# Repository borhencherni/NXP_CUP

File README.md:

**NXP Cup Robot**  
This repository contains the software, electronics, mechanical references, and documentation for the NXP Cup lane-following competition robot.  
   
 The current implementation is centered on two main embedded targets:  
- a Teensy 4.0 control unit that handles line tracking, steering, motor control, and telemetry generation  
- an ESP32 interface board that provides a web dashboard, manual drive controls, and live trajectory visualization  
**Project Overview 🤖**  
The robot is designed to follow a track as consistently and efficiently as possible while remaining debuggable during development.  
   
 The software is organized so that the core logic is separated into small header/source modules, making the control flow easier to maintain and inspect.  
   
 The goal of this document is to describe the robot, the role of each code part, and the current development phases in a way that matches the actual project structure.  
**System Architecture ⚙️**  
**Teensy 4.0 🧠**  
The Teensy is the main real-time controller. It is responsible for:  
- reading the Pixy2 line camera data  
- normalizing and fusing detected line vectors  
- computing a lookahead point for steering  
- applying PID-style steering correction  
- detecting lane sides and special line patterns  
- driving the motors and steering servo  
- reading the ultrasonic distance sensor  
- sending telemetry packets to the ESP32 over UART  
The Teensy code is organized into focused modules under NXPcup/include and NXPcup/src/teensy:  
- teensy_config.h for constants, pins, and tuning values  
- teensy_state.h and teensy_state.cpp for shared robot state  
- teensy_motors.h and teensy_motors.cpp for motor and servo output  
- teensy_sensors.h and teensy_sensors.cpp for ultrasonic sensing  
- teensy_vision.h and teensy_vision.cpp for Pixy2 processing and steering logic  
- main_teensy.cpp as the control entrypoint  
**ESP32 Interface 🌐**  
The ESP32 acts as the operator interface and telemetry gateway. It is responsible for:  
- receiving telemetry packets from the Teensy through UART  
- exposing a Wi-Fi access point  
- serving a browser-based control dashboard  
- sending manual drive commands back to the Teensy  
- drawing the robot trajectory in real time from received points  
The ESP32 code is organized into:  
- esp_config.h for UART and access point settings  
- esp_telemetry.h and esp_telemetry.cpp for packet parsing, point history, and command forwarding  
- esp_web.h and esp_web.cpp for the HTML interface and HTTP routes  
- main_esp.cpp as the entrypoint  
**Control Logic 🧭**  
The Teensy control loop follows a clear sequence:  
1. Read all Pixy2 line features  
2. Normalize line vector direction  
3. Fuse valid vectors into a single motion estimate  
4. Normalize the fused vector  
5. Compute an adaptive lookahead point  
6. Convert the lookahead error into steering correction  
7. Apply lane-side correction when only one side of the track is visible  
8. Clamp and smooth the servo command  
9. Drive the motors  
10. Send telemetry to the ESP32  
The telemetry packet format is:  
D,vx,vy,steeringangle,servoangle  
The ESP32 manual command format is:  
C,<command>  
Where the current commands are:  
- F for forward  
- B for backward  
- L for left  
- R for right  
- S for stop  
The current control strategy focuses on lane following and smooth steering.  
   
 The robot can be further developed by adding velocity regulation and speed profiling, in the style of the code asservissement vitesse approach, to keep the speed more stable across straights, curves, and transitions.  
**Phases Of Working 🔄**  
**1. Perception**  
The Pixy2 camera runs in line-tracking mode and the Teensy extracts track geometry from the visible vectors.  
   
 This phase focuses on identifying the path, rejecting noise, and understanding sharp turns, lane boundaries, and horizontal markers.  
**2. Motion Estimation**  
The detected vectors are filtered and fused into a single direction estimate.  
   
 A lookahead point is then computed so the robot can react smoothly on straights and more aggressively in curves.  
**3. Steering And Drive Control**  
The steering output is computed from the lookahead error and adjusted with PID-style terms.  
   
 The motor speed and servo angle are then constrained to keep motion stable.  
**4. Telemetry And Debugging**  
The Teensy sends live telemetry to the ESP32 so the robot can be observed while running.  
   
 This data includes vector direction, steering output, and servo angle.  
**5. Operator Interface**  
The ESP32 hosts a browser dashboard with manual drive buttons and a live trace of the robot path.  
   
 The LED status indicator changes color based on whether telemetry is being received.  
**6. Mechanical And Electrical Integration**  
The CAD, PCB, and wiring notes are used to assemble the chassis, sensors, drivetrain, and electronics reliably.  
   
 This phase ties the software to the physical robot.  
**Mechanical Part 🛠️**  
The mechanical part covers the chassis, steering, drivetrain, and mounting system.  
   
 These references are useful for assembly, servicing, and mechanical debugging.  
**Robot Assembly**  
**Mechanical Design**  
**Electrical Part ⚡**  
The electrical part covers the wiring, PCB layout, power distribution, and interface hardware.  
   
 These elements support the sensors, controller, motor driver, and communication links.  
**System Schematic**  
**PCB Routing**  
**PCB Overview**  
**Validation Videos 🎥**  
The following videos are used to validate different layers of the system during development:  
- video for the robot completing one lap.mp4 for the robot completing one lap  
- video for the robot stopping when detecting the box.mp4 for the robot stopping test  
**Pins And Hardware Notes 📌**  
Current Teensy pin usage:  
- motor inputs: 22, 23, 6, 7  
- servo output: 8  
- ultrasonic trigger: 18  
- ultrasonic echo: 19  
The project uses:  
- Teensy 4.0 as the controller  
- Pixy2 in line mode  
- steering servo  
- H-bridge motor driver  
- ultrasonic distance sensor  
- ESP32 for telemetry and control UI  
**Web Interface 🖥️**  
The ESP32 dashboard uses a dark industrial theme based on black, white, and #AA0000 red accents.  
   
 It includes:  
- forward, backward, left, right, and stop buttons  
- a circular ESP badge with a connection LED  
- live telemetry readouts  
- a black canvas with a white trail showing the robot path in real time  
**Web Interface Preview**  
**Software Layout 💻**  
The main source folders are:  
- NXPcup/src/teensy for the Teensy 4.0 control code  
- NXPcup/src/esp for the ESP32 dashboard and UART bridge  
- NXPcup/include for shared headers and configuration  
- NXPcup/lib for legacy or reusable helper sources  
- notes for pinout and power notes  
- Mécanique for CAD and mechanical references  
**Code Roles 🧩**  
The code is split so each module has a clear role in the robot:  
- main_teensy.cpp runs the full real-time control loop and coordinates perception, steering, drive output, and telemetry  
- teensy_vision.cpp handles Pixy2 processing, vector fusion, lane detection, and steering computation  
- teensy_motors.cpp converts high-level speed commands into motor outputs and servo control  
- teensy_sensors.cpp reads the ultrasonic sensor used for distance checking  
- teensy_state.cpp stores the shared robot state used by the other Teensy modules  
- main_esp.cpp initializes the ESP32 system and connects the web dashboard to UART telemetry  
- esp_telemetry.cpp parses telemetry packets, stores path points, and forwards manual commands  
- esp_web.cpp serves the browser interface, controls the buttons, and draws the live ride trace  
**Development Note 🚀**  
The robot can also be extended with velocity regulation and speed profiling in the style of code asservissement vitesse to stabilize motion across straights, curves, and transitions.  
**Power And Wiring Notes 🔌**  
The project notes indicate the following supply plan:  
- Teensy: 5V  
- camera: external 5V  
- servo: external 5V  
- motors: 12V  
- ultrasonic sensor: 3.3V  
- logic and power grounds must be shared where required  
**Build And Run 🏗️**  
The PlatformIO project is configured for the Teensy environment in NXPcup/platformio.ini.  
   
 Typical workflow:  
1. open the NXPcup folder in PlatformIO or VS Code  
2. build the Teensy environment  
3. upload to the Teensy board  
4. power the ESP32 and open the Wi-Fi dashboard  
5. watch the telemetry stream and path trace in the browser  
Example build command:  
cd NXPcup  
 platformio run -e teensy40  
   
**Resources 📚**  
- [Enseirb NXP Cup 2019 ](https://github.com/Enseirb-NXP-Cup-2019/cars/blob/master/src/Arduino/suivi_piste.ino "https://github.com/Enseirb-NXP-Cup-2019/cars/blob/master/src/Arduino/suivi_piste.ino")  
- [Enseirb NXP Cup 2019 website](https://github.com/Enseirb-NXP-Cup-2019/nxpcup.enseirb.github.io?tab=readme-ov-file "https://github.com/Enseirb-NXP-Cup-2019/nxpcup.enseirb.github.io?tab=readme-ov-file")  
- [Electromaker NXP Cup project](https://www.electromaker.io/project/view/nxp-cup-project "https://www.electromaker.io/project/view/nxp-cup-project")  
- [NXP-CUP-FINALS](https://github.com/aminebensaid66/NXP-CUP-FINALS "https://github.com/aminebensaid66/NXP-CUP-FINALS")  
**Notes 📝**  
This documentation reflects the current modularized Teensy and ESP32 codebase.  
   
 It is intended to help with debugging, maintenance, and competition preparation by keeping the code paths, hardware roles, and project assets in one place.  
   
   
 This work was done by the team members :  
   
 - Borhen CHERNI  
 - Mahmoud SOUABNI  
 - Meher LAHWAR

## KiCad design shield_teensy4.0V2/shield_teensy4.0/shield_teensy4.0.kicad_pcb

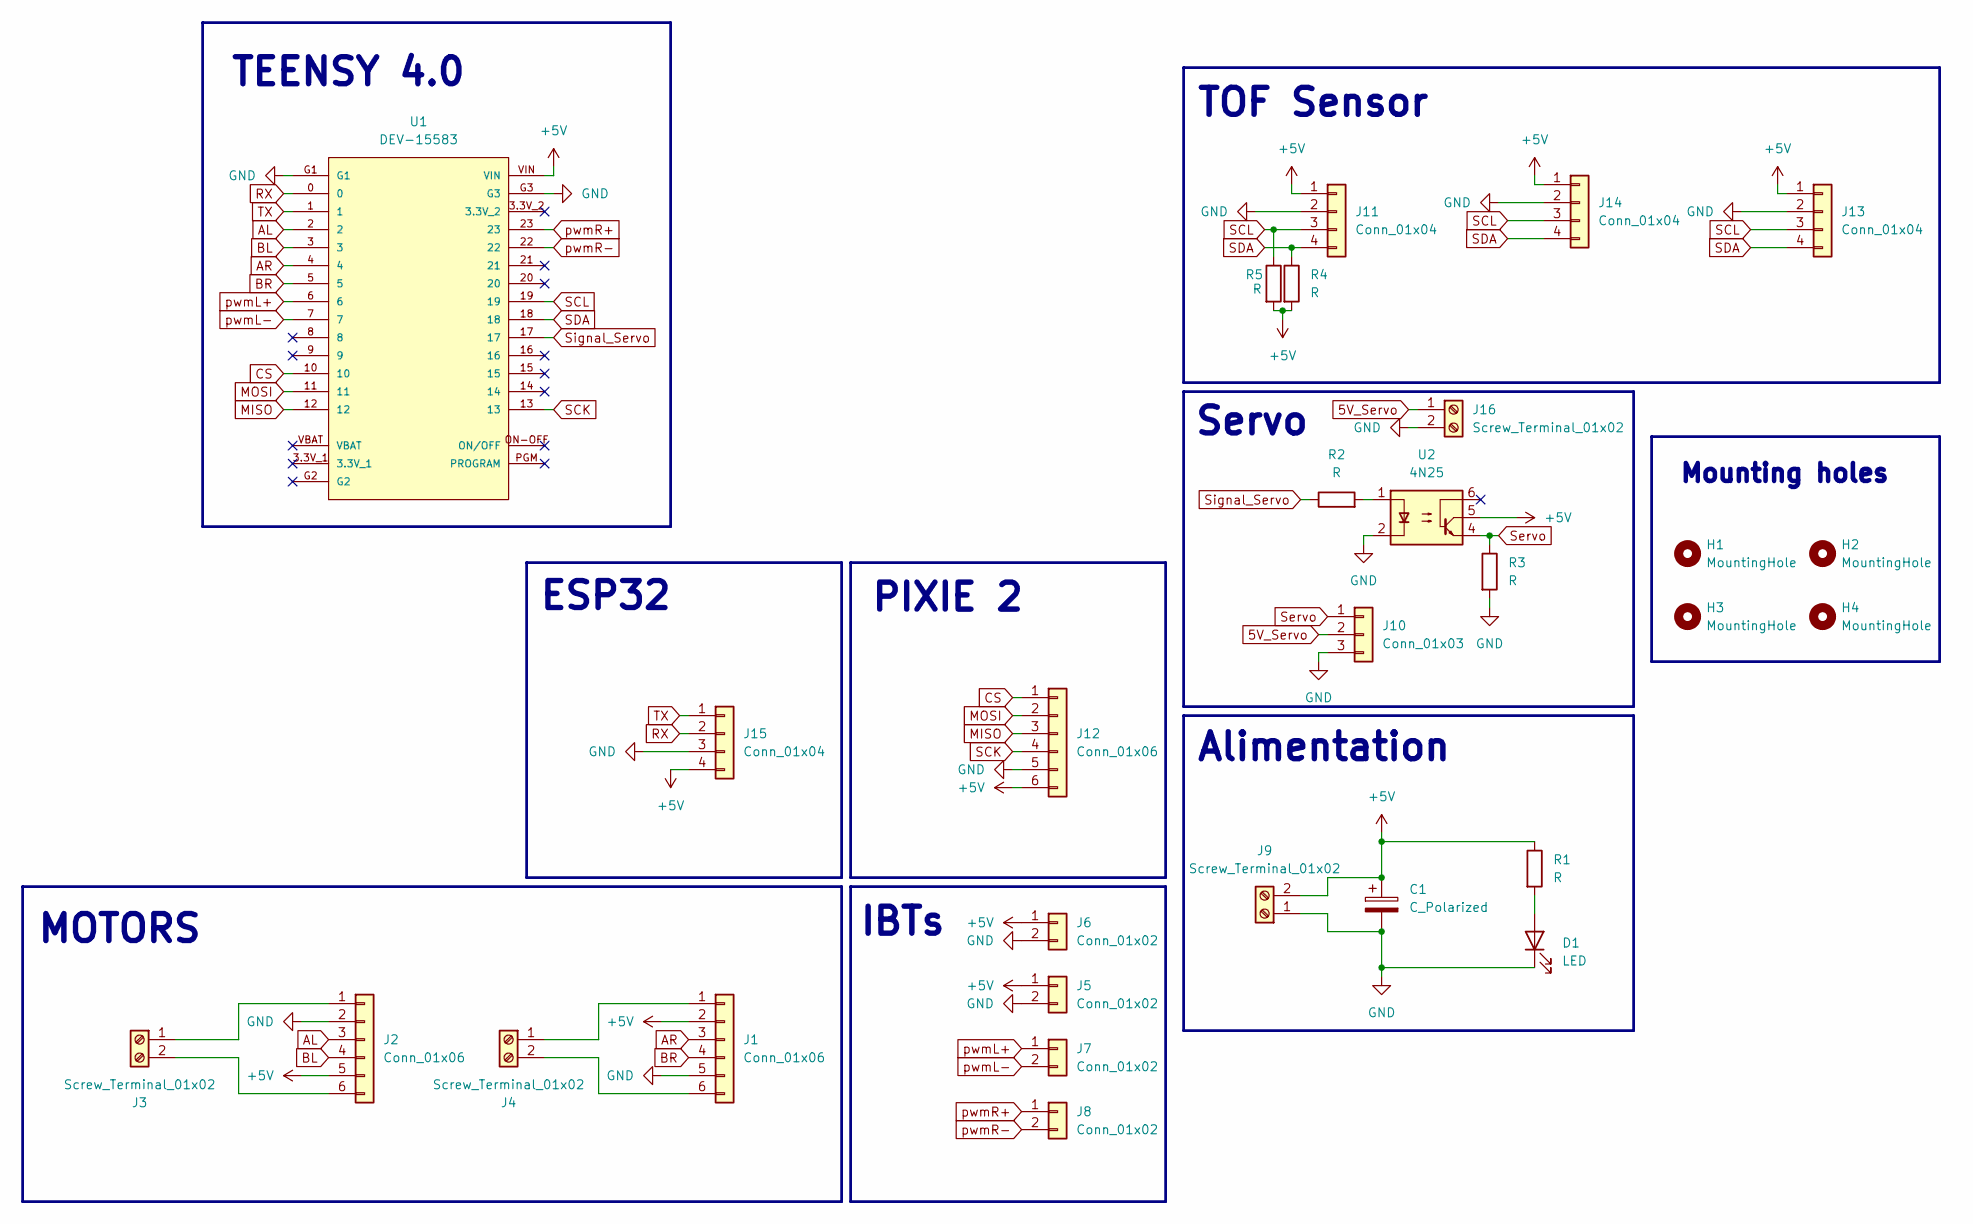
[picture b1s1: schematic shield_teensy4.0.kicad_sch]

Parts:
C1: C_Polarized; CP_Radial_D5.0mm_P2.50mm
D1: LED; LED_D3.0mm
H1, H2, H3, H4: MountingHole; MountingHole_3mm
J1, J2, J12: Conn_01x06; JST_XH_B6B-XH-A_1x06_P2.50mm_Vertical
J3, J4, J9, J16: Screw_Terminal_01x02; TerminalBlock_Phoenix_MKDS-1,5-2_1x02_P5.00mm_Horizontal
J5, J6, J7, J8: Conn_01x02; JST_XH_B2B-XH-A_1x02_P2.50mm_Vertical
J10: Conn_01x03; JST_XH_B3B-XH-A_1x03_P2.50mm_Vertical
J11, J13, J14, J15: Conn_01x04; JST_XH_B4B-XH-A_1x04_P2.50mm_Vertical
R1, R2, R3, R4, R5: R; R_Axial_DIN0204_L3.6mm_D1.6mm_P5.08mm_Horizontal
U1: DEV-15583; MODULE_DEV-15583
U2: 4N25; DIP-6_W7.62mm

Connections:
5V_Servo: J10.2, J16.1
+5V: C1.1, J1.2, J2.5, J5.1, J6.1, J9.2, J11.1, J12.6, J13.1, J14.1, J15.4, R1.1, R4.2, R5.2, U1.VIN, U2.5
AL: J2.3, U1.2
AR: J1.3, U1.4
BL: J2.4, U1.3
BR: J1.4, U1.5
CS: J12.1, U1.10
GND: C1.2, D1.1 (K), J1.5, J2.2, J5.2, J6.2, J9.1, J10.3, J11.2, J12.5, J13.2, J14.2, J15.3, J16.2, R3.2, U1.G1, U1.G3, U2.2
MISO: J12.3, U1.12
MOSI: J12.2, U1.11
unnamed: D1.2 (A), R1.2
unnamed: J1.1, J4.1
unnamed: J1.6, J4.2
unnamed: J2.1, J3.1
unnamed: J2.6, J3.2
unnamed: R2.2, U2.1
RX: J15.2, U1.0
SCK: J12.4, U1.13
SCL: J11.3, J13.3, J14.3, R5.1, U1.19
SDA: J11.4, J13.4, J14.4, R4.1, U1.18
Servo: J10.1, R3.1, U2.4
Signal_Servo: R2.1, U1.17
TX: J15.1, U1.1
pwmL+: J7.1, U1.6
pwmL-: J7.2, U1.7
pwmR+: J8.1, U1.23
pwmR-: J8.2, U1.22

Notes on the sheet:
MOTORS
IBTs
Mounting holes
ESP32
Alimentation
Servo
TEENSY 4.0
PIXIE 2
TOF Sensor

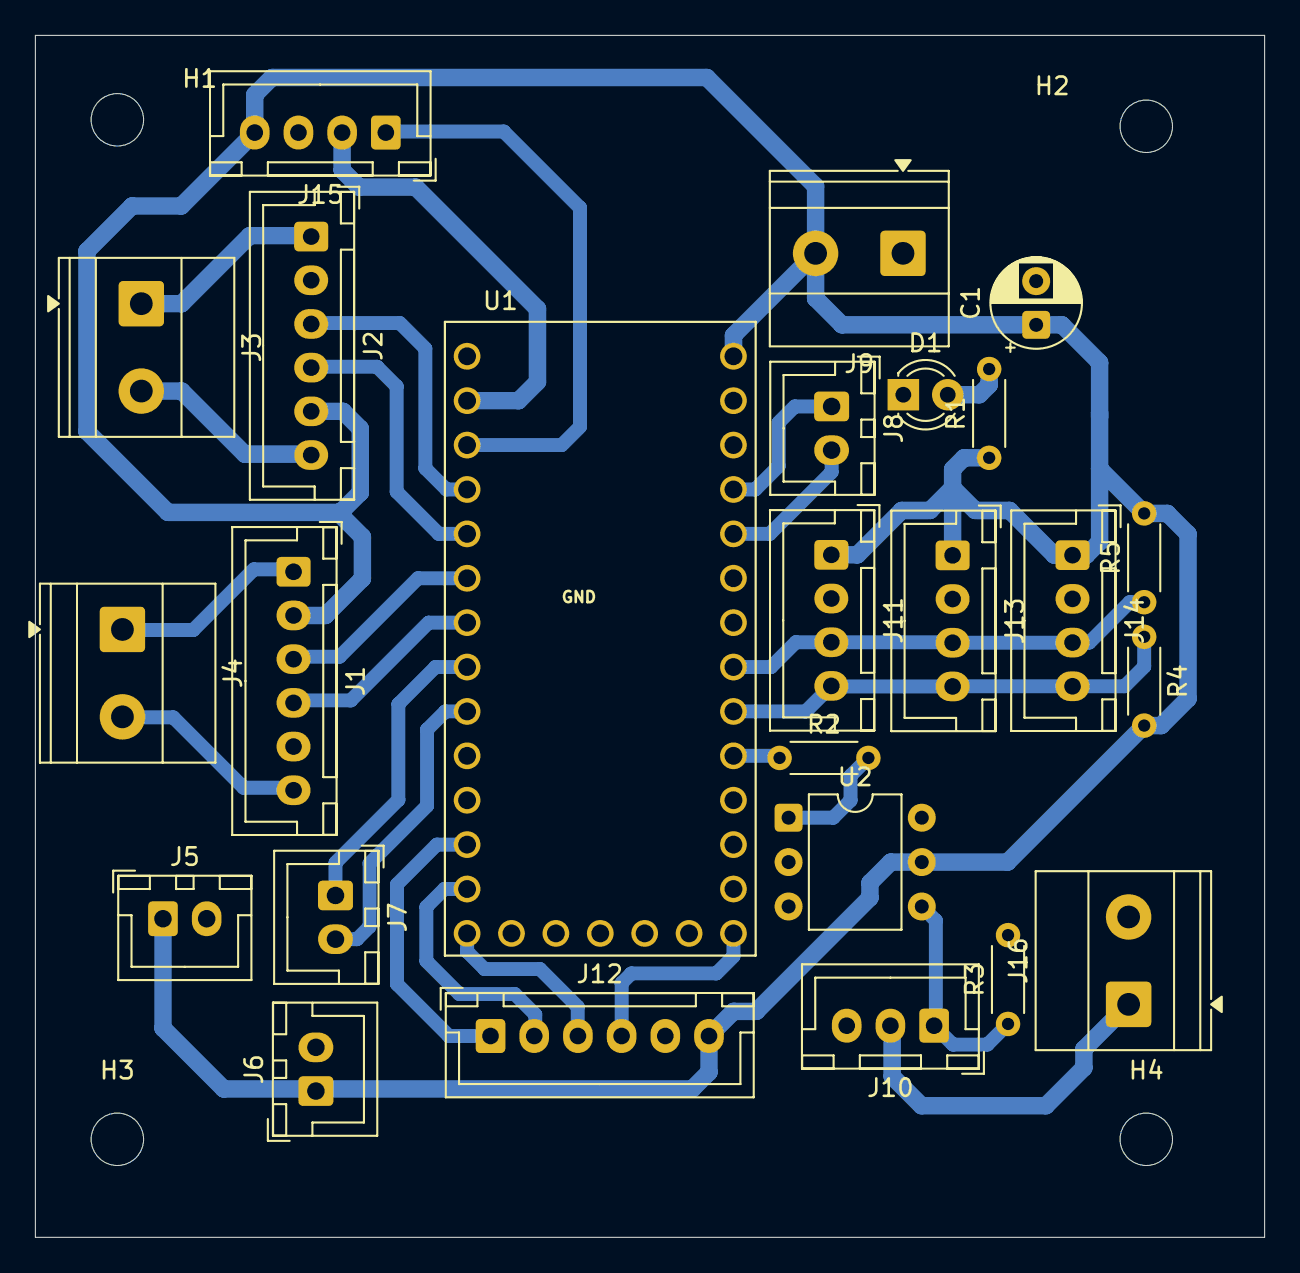
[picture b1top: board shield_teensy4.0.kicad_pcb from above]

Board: 2 copper layers, 70.3 x 68.8 mm, 29 parts (0 on the bottom side), 27 nets.

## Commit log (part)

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2026-03-10 Initial commit NXP cup
2026-03-11 chwaya updates
2026-03-11 adding first esp code
2026-03-16 previous work organized
2026-03-17 tabdil pinout w chwaya fazet
2026-03-17 asser vitesse
2026-03-18 last updates
2026-03-18 code testtotal
2026-03-18 runMotors public to avoid speed control
2026-03-18 beginning to adapt
2026-03-18 added new vision approch
2026-03-18 values change
2026-03-19 some changes that gave the best tests
2026-04-02 awel code bel pcb jdida
2026-04-03 a method try on intersection detection
2026-04-03 changed PINS
2026-04-05 last changes
2026-04-05 last code with ultrason
2026-04-05 Kp&Kd changes
2026-04-07 test
2026-04-07 functional code pass the intersection but gets lost after it
2026-04-08 tarki7 bel servo buffer
2026-04-08 code ykhadem
2026-04-08 yfawet el intersection
2026-04-09 ekher code ymachi fi test
2026-04-09 code sbeh
2026-05-18 Final updates
2026-05-18 Added other vision approach
